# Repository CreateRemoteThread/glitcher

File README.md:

# glitcher

## Introduction

Glitcher is a homebrew fault injection system, built around a Pi Pico and CMOD A7, with a MAX4619 and an irf7807 providing multiplexer and crowbar mosfet style glitching respectively. Generous GPIO (FPGA + Pi Pico) + SMA outputs are available.

This project is heavily inspired by the ChipWhisperer set of products.

## Use

The Pi Pico is the simplest method of using this. Using a micro USB cable, access the MicroPython interface and use the glitcher library to control the FPGA's default firmware:

```
import glitcher

g = glitcher.Glitcher()
g.enablemux(True)                # enable max4619. crowbar always "on"
g.setmask(glitcher.SELECT_MOSFET)         # select mosfet for glitching
g.muxout(glitcher.SELECT_MUXA)            # switch x_out to x1
g.muxout(glitcher.SELECT_NONE)            # switch x_out to x0
g.rnr(delay=5,width=5)           # write delay/width, glitch output according to setmask
```

The Pi Pico uses only a serial port to talk to the FPGA at 115200bps, so you can swap it for some other uC / make a shield / whatever. Just replace self.u1 with a pyserial output if you want to use a control PC (enablemux is the only thing requiring the pi pico, just hardwire it idk).

Probably don't use g.muxout(0xF) - but do whatever you want.

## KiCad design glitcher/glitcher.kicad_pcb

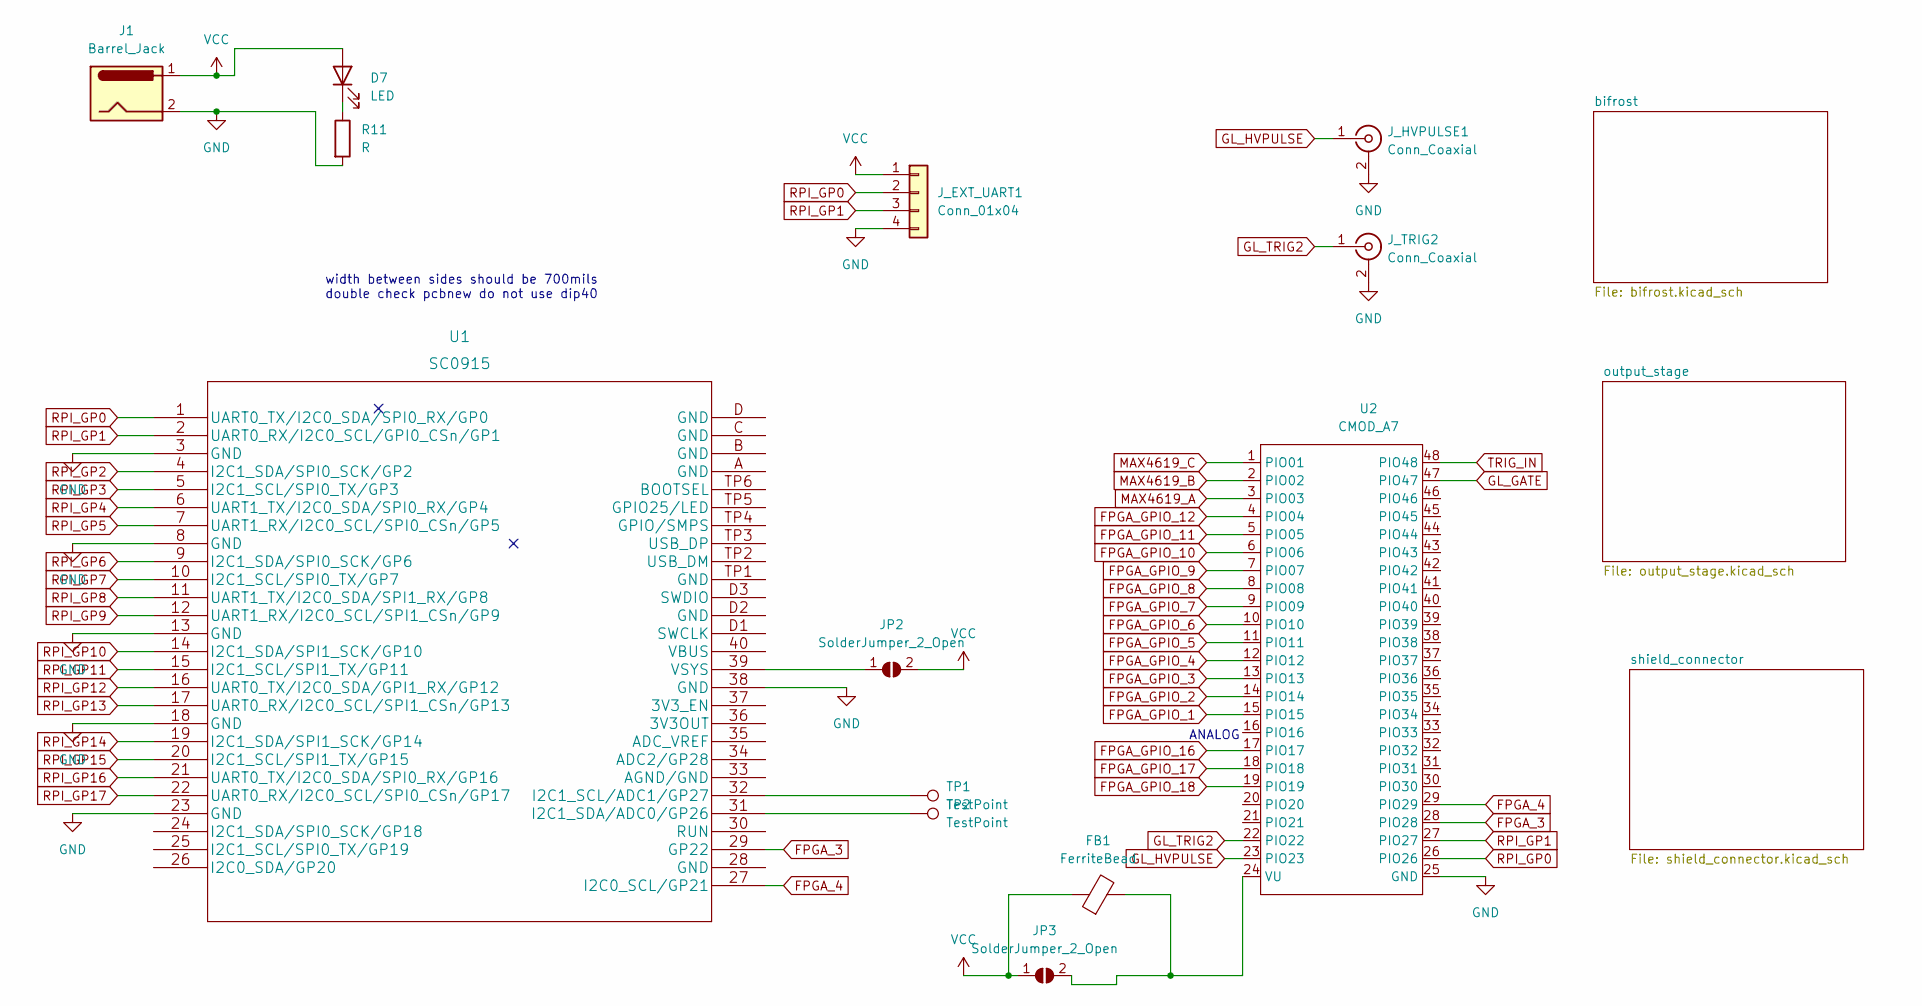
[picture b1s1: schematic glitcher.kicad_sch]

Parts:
D7: LED; LED_0603_1608Metric
FB1: FerriteBead; L_0805_2012Metric_Pad1.05x1.20mm_HandSolder
J1: Barrel_Jack; BarrelJack_Horizontal
JP2, JP3: SolderJumper_2_Open; SolderJumper-2_P1.3mm_Open_Pad1.0x1.5mm
J_EXT_UART1: Conn_01x04; PinHeader_1x04_P2.54mm_Vertical
J_HVPULSE1: Conn_Coaxial; RF2-04A-T-00-50-G
J_TRIG2: Conn_Coaxial; RF2-04A-T-00-50-G
R11: R; R_0603_1608Metric
TP1, TP2: TestPoint; TestPoint_Pad_D3.0mm
U1: SC0915; rpi_socket_fixed
U2: CMOD_A7; DIP-48_W15.24mm_Socket_LongPads

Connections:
FPGA_3: U1.29 (GP22), U2.28 (PIO28)
FPGA_4: U1.27 (I2C0_SCL/GP21), U2.29 (PIO29)
FPGA_GPIO_1: U2.15 (PIO15)
FPGA_GPIO_2: U2.14 (PIO14); also elsewhere on the board
FPGA_GPIO_3: U2.13 (PIO13); also elsewhere on the board
FPGA_GPIO_4: U2.12 (PIO12); also elsewhere on the board
FPGA_GPIO_5: U2.11 (PIO11); also elsewhere on the board
FPGA_GPIO_6: U2.10 (PIO10); also elsewhere on the board
FPGA_GPIO_7: U2.9 (PIO09); also elsewhere on the board
FPGA_GPIO_8: U2.8 (PIO08); also elsewhere on the board
FPGA_GPIO_9: U2.7 (PIO07); also elsewhere on the board
FPGA_GPIO_10: U2.6 (PIO06); also elsewhere on the board
FPGA_GPIO_11: U2.5 (PIO05); also elsewhere on the board
FPGA_GPIO_12: U2.4 (PIO04); also elsewhere on the board
FPGA_GPIO_16: U2.17 (PIO17); also elsewhere on the board
FPGA_GPIO_17: U2.18 (PIO18); also elsewhere on the board
FPGA_GPIO_18: U2.19 (PIO19); also elsewhere on the board
GL_GATE: U2.47 (PIO47); also elsewhere on the board
GL_HVPULSE: J_HVPULSE1.1 (In), U2.23 (PIO23)
GL_TRIG2: J_TRIG2.1 (In), U2.22 (PIO22)
GND: J1.2, J_EXT_UART1.4, J_HVPULSE1.2 (Ext), J_HVPULSE1.3, J_HVPULSE1.4, J_HVPULSE1.5, J_TRIG2.2 (Ext), J_TRIG2.3, J_TRIG2.4, J_TRIG2.5, R11.2, U1.3 (GND), U1.8 (GND), U1.13 (GND), U1.18 (GND), U1.23 (GND), U1.38 (GND), U2.25 (GND); also elsewhere on the board
MAX4619_A: U2.3 (PIO03); also elsewhere on the board
MAX4619_B: U2.2 (PIO02); also elsewhere on the board
MAX4619_C: U2.1 (PIO01); also elsewhere on the board
unnamed: D7.1 (K), R11.1
unnamed: FB1.2, JP3.2 (B), U2.24 (VU)
unnamed: JP2.1 (A), U1.39 (VSYS)
unnamed: TP1.1, U1.32 (I2C1_SCL/ADC1/GP27)
unnamed: TP2.1, U1.31 (I2C1_SDA/ADC0/GP26)
RPI_GP0: J_EXT_UART1.2, U1.1 (UART0_TX/I2C0_SDA/SPI0_RX/GP0), U2.26 (PIO26)
RPI_GP1: J_EXT_UART1.3, U1.2 (UART0_RX/I2C0_SCL/GPI0_CSn/GP1), U2.27 (PIO27)
RPI_GP2: U1.4 (I2C1_SDA/SPI0_SCK/GP2); also elsewhere on the board
RPI_GP3: U1.5 (I2C1_SCL/SPI0_TX/GP3); also elsewhere on the board
RPI_GP4: U1.6 (UART1_TX/I2C0_SDA/SPI0_RX/GP4); also elsewhere on the board
RPI_GP5: U1.7 (UART1_RX/I2C0_SCL/SPI0_CSn/GP5); also elsewhere on the board
RPI_GP6: U1.9 (I2C1_SDA/SPI0_SCK/GP6); also elsewhere on the board
RPI_GP7: U1.10 (I2C1_SCL/SPI0_TX/GP7); also elsewhere on the board
RPI_GP8: U1.11 (UART1_TX/I2C0_SDA/SPI1_RX/GP8); also elsewhere on the board
RPI_GP9: U1.12 (UART1_RX/I2C0_SCL/SPI1_CSn/GP9); also elsewhere on the board
RPI_GP10: U1.14 (I2C1_SDA/SPI1_SCK/GP10); also elsewhere on the board
RPI_GP11: U1.15 (I2C1_SCL/SPI1_TX/GP11); also elsewhere on the board
RPI_GP12: U1.16 (UART0_TX/I2C0_SDA/GPI1_RX/GP12); also elsewhere on the board
RPI_GP13: U1.17 (UART0_RX/I2C0_SCL/SPI1_CSn/GP13); also elsewhere on the board
RPI_GP14: U1.19 (I2C1_SDA/SPI1_SCK/GP14); also elsewhere on the board
RPI_GP15: U1.20 (I2C1_SCL/SPI1_TX/GP15); also elsewhere on the board
RPI_GP16: U1.21 (UART0_TX/I2C0_SDA/SPI0_RX/GP16)
RPI_GP17: U1.22 (UART0_RX/I2C0_SCL/SPI0_CSn/GP17)
TRIG_IN: U2.48 (PIO48); also elsewhere on the board
VCC: D7.2 (A), FB1.1, J1.1, JP2.2 (B), JP3.1 (A), J_EXT_UART1.1; also elsewhere on the board

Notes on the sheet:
width between sides should be 700mils double check pcbnew do not use dip40
ANALOG

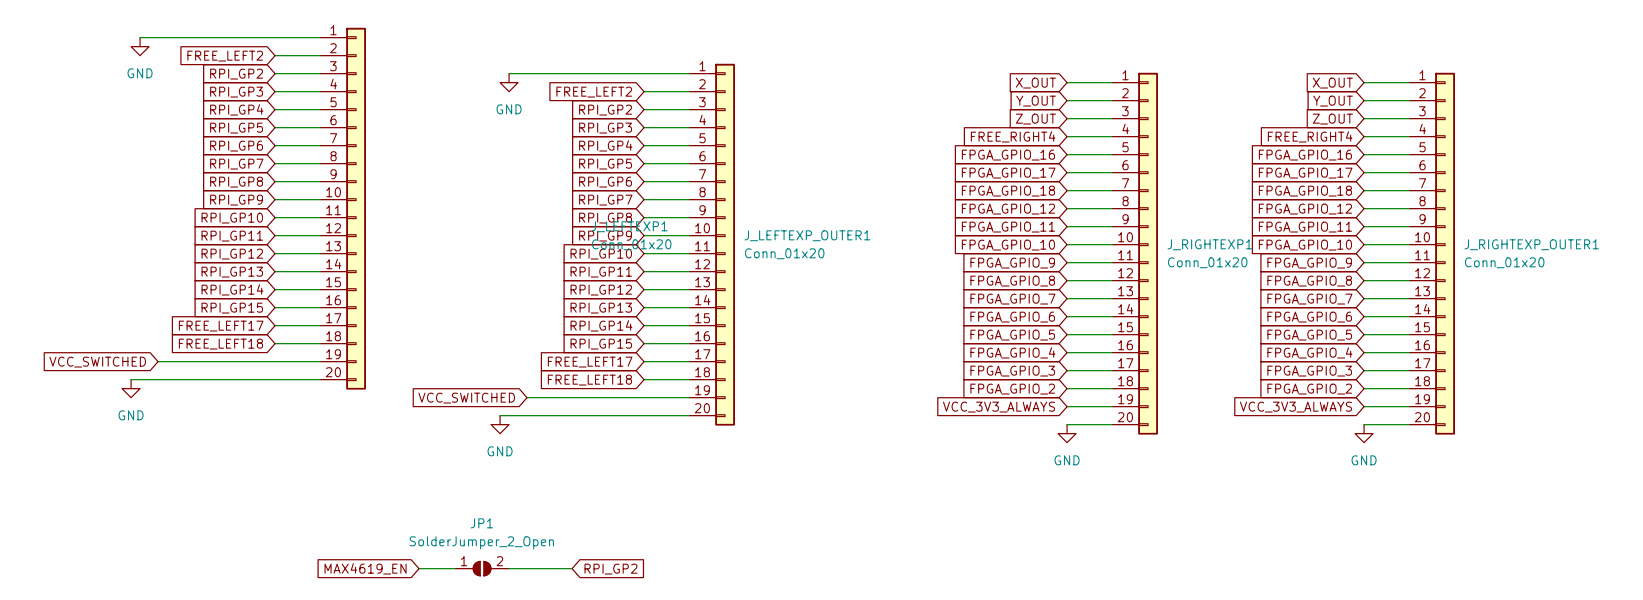
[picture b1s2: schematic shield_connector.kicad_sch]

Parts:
JP1: SolderJumper_2_Open; SolderJumper-2_P1.3mm_Open_RoundedPad1.0x1.5mm
J_LEFTEXP1: Conn_01x20; PinHeader_1x20_P2.54mm_Vertical
J_LEFTEXP_OUTER1: Conn_01x20; PinHeader_1x20_P2.54mm_Vertical
J_RIGHTEXP1: Conn_01x20; PinHeader_1x20_P2.54mm_Vertical
J_RIGHTEXP_OUTER1: Conn_01x20; PinHeader_1x20_P2.54mm_Vertical

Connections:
FPGA_GPIO_2: J_RIGHTEXP1.18, J_RIGHTEXP_OUTER1.18; also elsewhere on the board
FPGA_GPIO_3: J_RIGHTEXP1.17, J_RIGHTEXP_OUTER1.17; also elsewhere on the board
FPGA_GPIO_4: J_RIGHTEXP1.16, J_RIGHTEXP_OUTER1.16; also elsewhere on the board
FPGA_GPIO_5: J_RIGHTEXP1.15, J_RIGHTEXP_OUTER1.15; also elsewhere on the board
FPGA_GPIO_6: J_RIGHTEXP1.14, J_RIGHTEXP_OUTER1.14; also elsewhere on the board
FPGA_GPIO_7: J_RIGHTEXP1.13, J_RIGHTEXP_OUTER1.13; also elsewhere on the board
FPGA_GPIO_8: J_RIGHTEXP1.12, J_RIGHTEXP_OUTER1.12; also elsewhere on the board
FPGA_GPIO_9: J_RIGHTEXP1.11, J_RIGHTEXP_OUTER1.11; also elsewhere on the board
FPGA_GPIO_10: J_RIGHTEXP1.10, J_RIGHTEXP_OUTER1.10; also elsewhere on the board
FPGA_GPIO_11: J_RIGHTEXP1.9, J_RIGHTEXP_OUTER1.9; also elsewhere on the board
FPGA_GPIO_12: J_RIGHTEXP1.8, J_RIGHTEXP_OUTER1.8; also elsewhere on the board
FPGA_GPIO_16: J_RIGHTEXP1.5, J_RIGHTEXP_OUTER1.5; also elsewhere on the board
FPGA_GPIO_17: J_RIGHTEXP1.6, J_RIGHTEXP_OUTER1.6; also elsewhere on the board
FPGA_GPIO_18: J_RIGHTEXP1.7, J_RIGHTEXP_OUTER1.7; also elsewhere on the board
FREE_LEFT2: J_LEFTEXP1.2, J_LEFTEXP_OUTER1.2
FREE_LEFT17: J_LEFTEXP1.17, J_LEFTEXP_OUTER1.17
FREE_LEFT18: J_LEFTEXP1.18, J_LEFTEXP_OUTER1.18
FREE_RIGHT4: J_RIGHTEXP1.4, J_RIGHTEXP_OUTER1.4
GND: J_LEFTEXP1.1, J_LEFTEXP1.20, J_LEFTEXP_OUTER1.1, J_LEFTEXP_OUTER1.20, J_RIGHTEXP1.20, J_RIGHTEXP_OUTER1.20; also elsewhere on the board
MAX4619_EN: JP1.1 (A); also elsewhere on the board
RPI_GP2: JP1.2 (B), J_LEFTEXP1.3, J_LEFTEXP_OUTER1.3; also elsewhere on the board
RPI_GP3: J_LEFTEXP1.4, J_LEFTEXP_OUTER1.4; also elsewhere on the board
RPI_GP4: J_LEFTEXP1.5, J_LEFTEXP_OUTER1.5; also elsewhere on the board
RPI_GP5: J_LEFTEXP1.6, J_LEFTEXP_OUTER1.6; also elsewhere on the board
RPI_GP6: J_LEFTEXP1.7, J_LEFTEXP_OUTER1.7; also elsewhere on the board
RPI_GP7: J_LEFTEXP1.8, J_LEFTEXP_OUTER1.8; also elsewhere on the board
RPI_GP8: J_LEFTEXP1.9, J_LEFTEXP_OUTER1.9; also elsewhere on the board
RPI_GP9: J_LEFTEXP1.10, J_LEFTEXP_OUTER1.10; also elsewhere on the board
RPI_GP10: J_LEFTEXP1.11, J_LEFTEXP_OUTER1.11; also elsewhere on the board
RPI_GP11: J_LEFTEXP1.12, J_LEFTEXP_OUTER1.12; also elsewhere on the board
RPI_GP12: J_LEFTEXP1.13, J_LEFTEXP_OUTER1.13; also elsewhere on the board
RPI_GP13: J_LEFTEXP1.14, J_LEFTEXP_OUTER1.14; also elsewhere on the board
RPI_GP14: J_LEFTEXP1.15, J_LEFTEXP_OUTER1.15; also elsewhere on the board
RPI_GP15: J_LEFTEXP1.16, J_LEFTEXP_OUTER1.16; also elsewhere on the board
VCC_3V3_ALWAYS: J_RIGHTEXP1.19, J_RIGHTEXP_OUTER1.19; also elsewhere on the board
VCC_SWITCHED: J_LEFTEXP1.19, J_LEFTEXP_OUTER1.19; also elsewhere on the board
X_OUT: J_RIGHTEXP1.1, J_RIGHTEXP_OUTER1.1; also elsewhere on the board
Y_OUT: J_RIGHTEXP1.2, J_RIGHTEXP_OUTER1.2; also elsewhere on the board
Z_OUT: J_RIGHTEXP1.3, J_RIGHTEXP_OUTER1.3; also elsewhere on the board

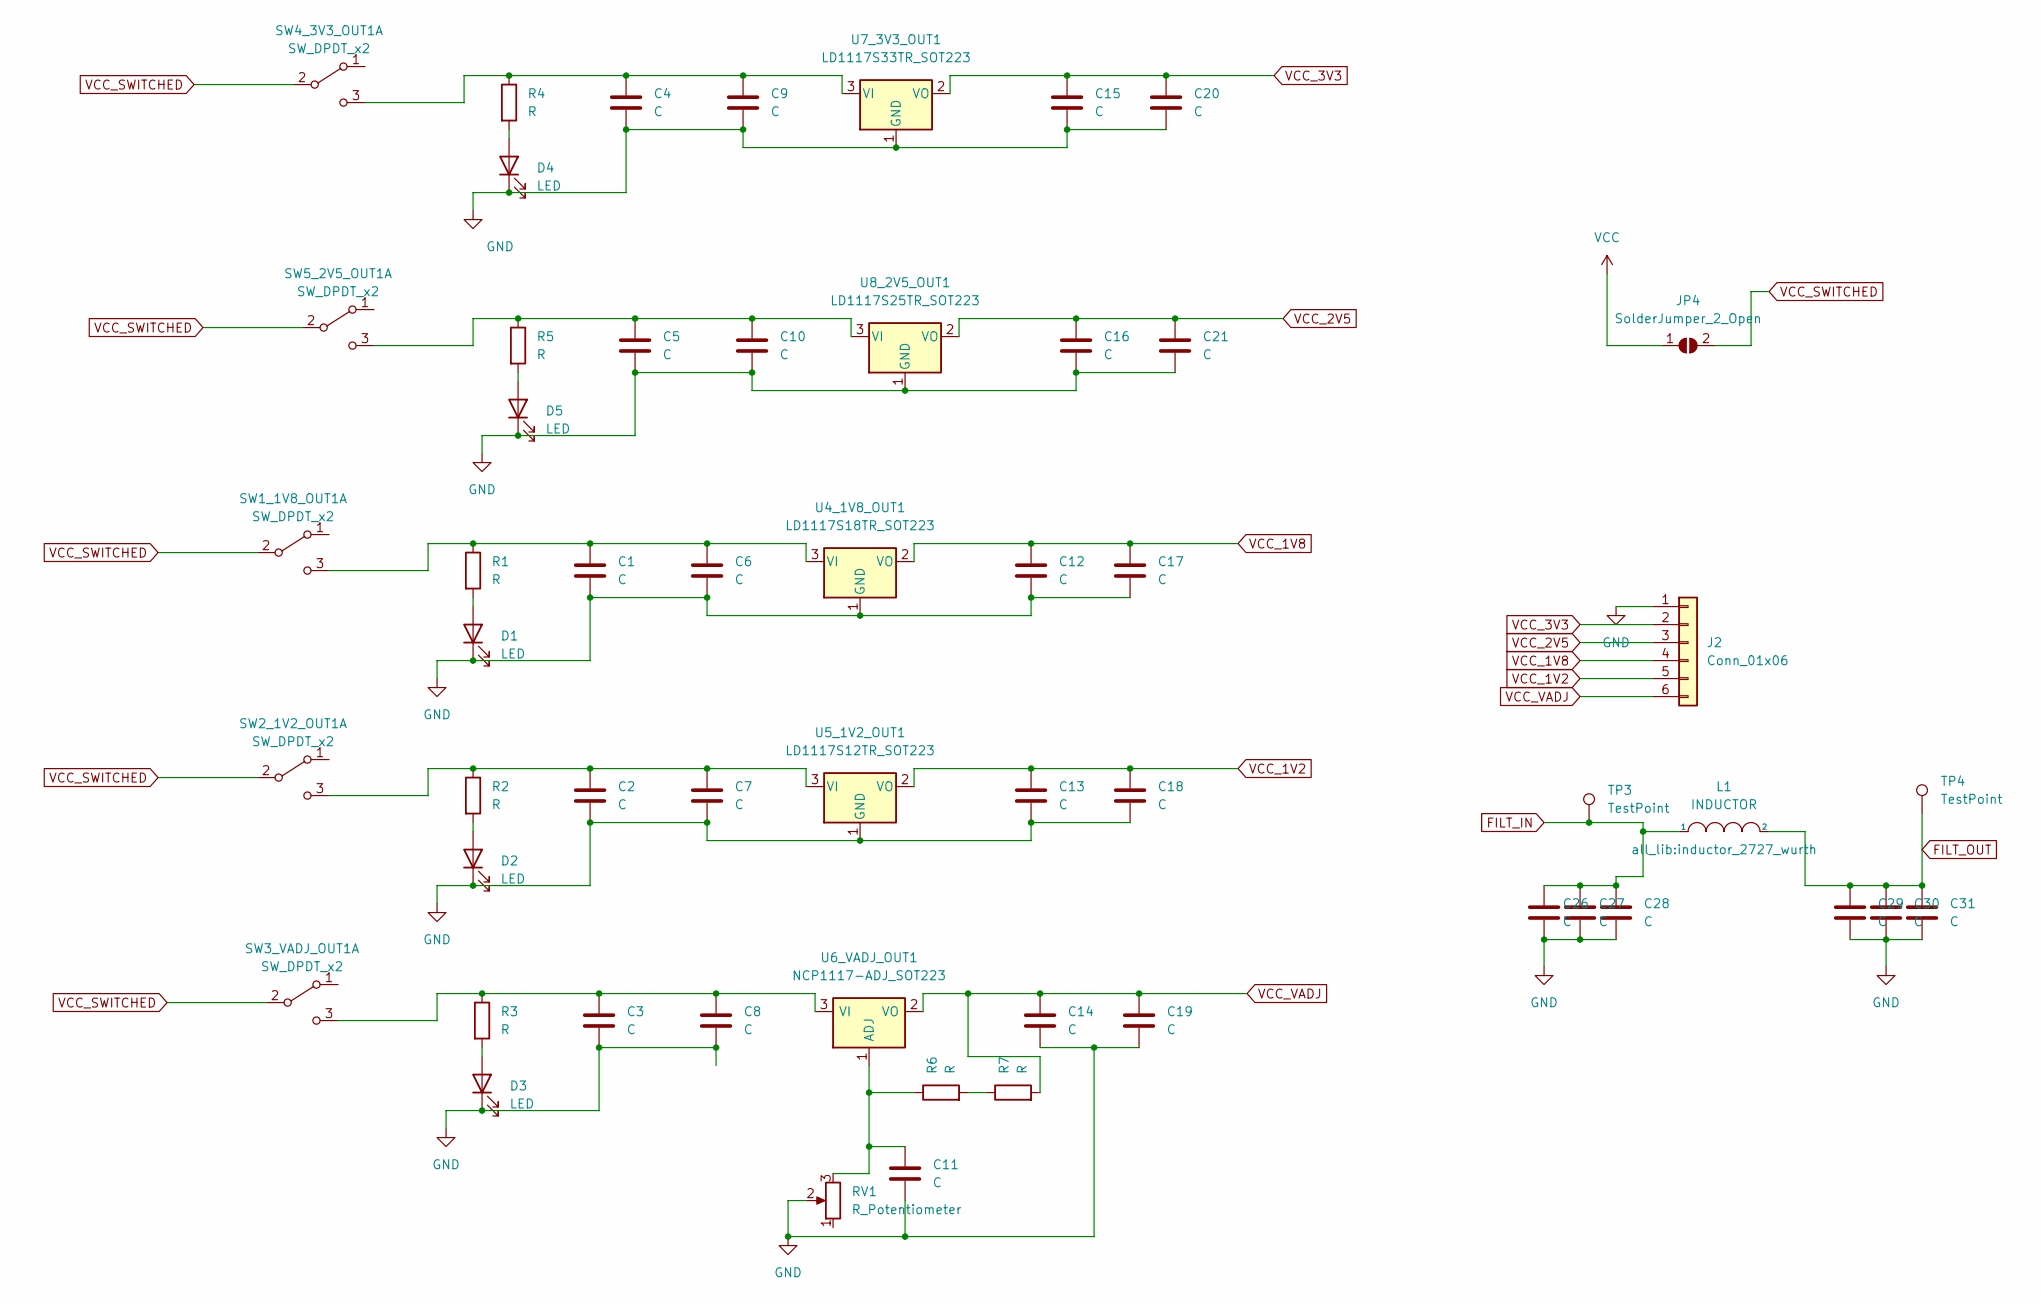
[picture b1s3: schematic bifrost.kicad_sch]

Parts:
C1, C2, C3, C4, C5, C6, C7, C8, C9, C10, C11, C12, C13, C14, C15, C16, C17, C18, C19, C20, C21, C26, C27, C28, C29, C30, C31: C; C_0603_1608Metric_Pad1.08x0.95mm_HandSolder
D1, D2, D3, D4, D5: LED; LED_0603_1608Metric_Pad1.05x0.95mm_HandSolder
J2: Conn_01x06; PinHeader_1x06_P2.54mm_Vertical
JP4: SolderJumper_2_Open; SolderJumper-2_P1.3mm_Open_RoundedPad1.0x1.5mm
L1: INDUCTOR; inductor_2727_wurth
R1, R2, R3, R4, R5, R6, R7: R; R_0603_1608Metric_Pad0.98x0.95mm_HandSolder
RV1: R_Potentiometer; TRIM_3361P-1-501GLF
SW1_1V8_OUT1, SW2_1V2_OUT1, SW3_VADJ_OUT1, SW4_3V3_OUT1, SW5_2V5_OUT1: SW_DPDT_x2; JS202011SCQN
TP3, TP4: TestPoint; TestPoint_Pad_D2.5mm
U4_1V8_OUT1: LD1117S18TR_SOT223; SOT-223-3_TabPin2
U5_1V2_OUT1: LD1117S12TR_SOT223; SOT-223-3_TabPin2
U6_VADJ_OUT1: NCP1117-ADJ_SOT223; SOT-223-3_TabPin2
U7_3V3_OUT1: LD1117S33TR_SOT223; SOT-223-3_TabPin2
U8_2V5_OUT1: LD1117S25TR_SOT223; SOT-223-3_TabPin2

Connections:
FILT_IN: C26.1, C27.1, C28.1, L1.1, TP3.1
FILT_OUT: C29.1, C30.1, C31.1, L1.2, TP4.1
GND: C1.2, C2.2, C3.2, C4.2, C5.2, C6.2, C7.2, C8.2, C9.2, C10.2, C11.2, C12.2, C13.2, C14.2, C15.2, C16.2, C17.2, C18.2, C19.2, C20.2, C21.2, C26.2, C27.2, C28.2, C29.2, C30.2, C31.2, D1.1 (K), D2.1 (K), D3.1 (K), D4.1 (K), D5.1 (K), J2.1, RV1.2, U4_1V8_OUT1.1 (GND), U5_1V2_OUT1.1 (GND), U7_3V3_OUT1.1 (GND), U8_2V5_OUT1.1 (GND); also elsewhere on the board
unnamed: C1.1, C6.1, R1.1, SW1_1V8_OUT1.3 (C), U4_1V8_OUT1.3 (VI)
unnamed: C2.1, C7.1, R2.1, SW2_1V2_OUT1.3 (C), U5_1V2_OUT1.3 (VI)
unnamed: C3.1, C8.1, R3.1, SW3_VADJ_OUT1.3 (C), U6_VADJ_OUT1.3 (VI)
unnamed: C4.1, C9.1, R4.1, SW4_3V3_OUT1.3 (C), U7_3V3_OUT1.3 (VI)
unnamed: C5.1, C10.1, R5.1, SW5_2V5_OUT1.3 (C), U8_2V5_OUT1.3 (VI)
unnamed: C11.1, R6.1, RV1.3, U6_VADJ_OUT1.1 (ADJ)
unnamed: D1.2 (A), R1.2
unnamed: D2.2 (A), R2.2
unnamed: D3.2 (A), R3.2
unnamed: D4.2 (A), R4.2
unnamed: D5.2 (A), R5.2
unnamed: R6.2, R7.1
VCC: JP4.1 (A); also elsewhere on the board
VCC_1V2: C13.1, C18.1, J2.5, U5_1V2_OUT1.2 (VO)
VCC_1V8: C12.1, C17.1, J2.4, U4_1V8_OUT1.2 (VO)
VCC_2V5: C16.1, C21.1, J2.3, U8_2V5_OUT1.2 (VO)
VCC_3V3: C15.1, C20.1, J2.2, U7_3V3_OUT1.2 (VO)
VCC_SWITCHED: JP4.2 (B), SW1_1V8_OUT1.2 (B), SW2_1V2_OUT1.2 (B), SW3_VADJ_OUT1.2 (B), SW4_3V3_OUT1.2 (B), SW5_2V5_OUT1.2 (B); also elsewhere on the board
VCC_VADJ: C14.1, C19.1, J2.6, R7.2, U6_VADJ_OUT1.2 (VO)

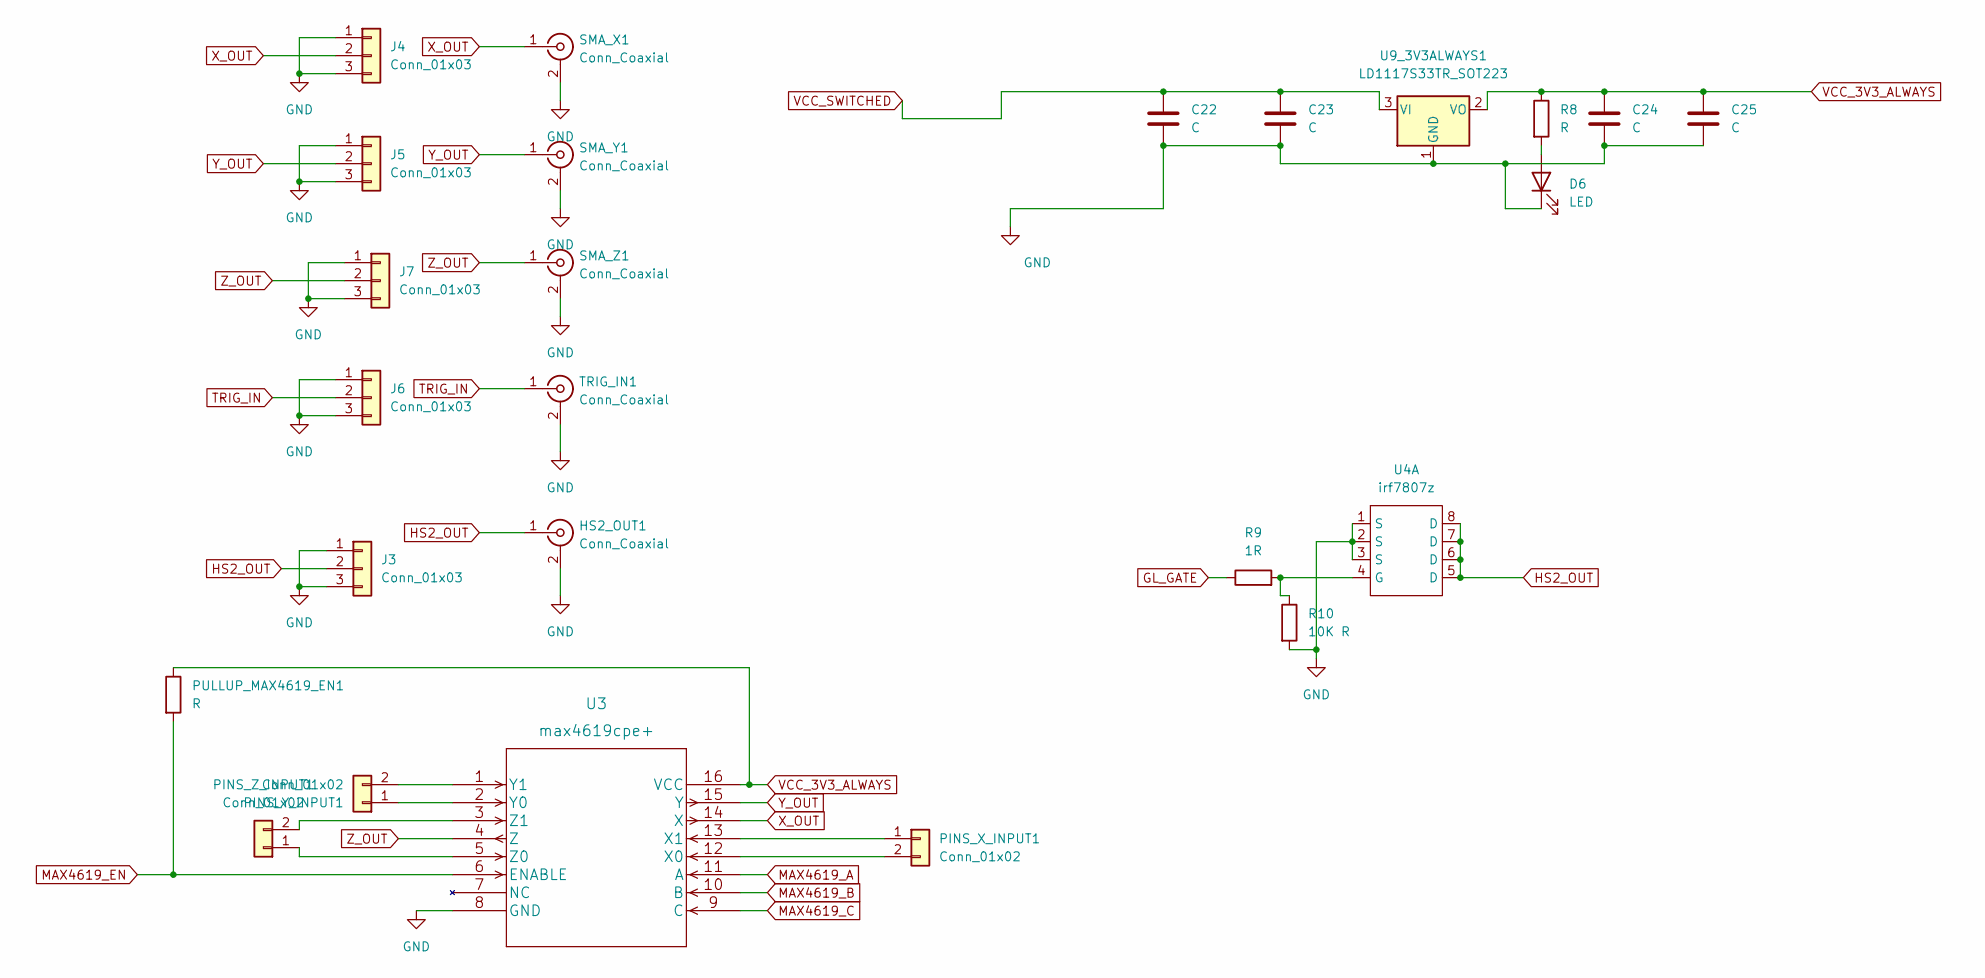
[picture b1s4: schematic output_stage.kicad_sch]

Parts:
C22, C23, C24, C25: C; C_0603_1608Metric_Pad1.08x0.95mm_HandSolder
D6: LED; LED_0603_1608Metric_Pad1.05x0.95mm_HandSolder
HS2_OUT1: Conn_Coaxial; SMA_Molex_73251-2120_EdgeMount_Horizontal
J3, J4, J5, J6, J7: Conn_01x03; PinHeader_1x03_P2.54mm_Vertical
PINS_X_INPUT1: Conn_01x02; PinHeader_1x02_P2.54mm_Vertical
PINS_Y_INPUT1: Conn_01x02; PinHeader_1x02_P2.54mm_Vertical
PINS_Z_INPUT1: Conn_01x02; PinHeader_1x02_P2.54mm_Vertical
PULLUP_MAX4619_EN1: R; R_0603_1608Metric_Pad0.98x0.95mm_HandSolder
R8: R; R_0603_1608Metric_Pad0.98x0.95mm_HandSolder
R9: 1R; R_0603_1608Metric_Pad0.98x0.95mm_HandSolder
R10: 10K R; R_0603_1608Metric_Pad0.98x0.95mm_HandSolder
SMA_X1: Conn_Coaxial; SMA_Molex_73251-2120_EdgeMount_Horizontal
SMA_Y1: Conn_Coaxial; SMA_Molex_73251-2120_EdgeMount_Horizontal
SMA_Z1: Conn_Coaxial; SMA_Molex_73251-2120_EdgeMount_Horizontal
TRIG_IN1: Conn_Coaxial; SMA_Molex_73251-2120_EdgeMount_Horizontal
U3: max4619cpe+; DIP-16_W7.62mm_Socket_LongPads
U4: irf7807z; SOIC-8-1EP_3.9x4.9mm_P1.27mm_EP2.29x3mm
U9_3V3ALWAYS1: LD1117S33TR_SOT223; SOT-223-3_TabPin2

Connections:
GL_GATE: R9.1; also elsewhere on the board
GND: C22.2, C23.2, C24.2, C25.2, D6.1 (K), HS2_OUT1.2 (Ext), J3.1, J3.3, J4.1, J4.3, J5.1, J5.3, J6.1, J6.3, J7.1, J7.3, R10.2, SMA_X1.2 (Ext), SMA_Y1.2 (Ext), SMA_Z1.2 (Ext), TRIG_IN1.2 (Ext), U3.8 (GND), U4.1 (S), U4.2 (S), U4.3 (S), U9_3V3ALWAYS1.1 (GND); also elsewhere on the board
HS2_OUT: HS2_OUT1.1 (In), J3.2, U4.5 (D), U4.6 (D), U4.7 (D), U4.8 (D)
MAX4619_A: U3.11 (A); also elsewhere on the board
MAX4619_B: U3.10 (B); also elsewhere on the board
MAX4619_C: U3.9 (C); also elsewhere on the board
MAX4619_EN: PULLUP_MAX4619_EN1.2, U3.6 (ENABLE); also elsewhere on the board
unnamed: D6.2 (A), R8.2
unnamed: PINS_X_INPUT1.1, U3.13 (X1)
unnamed: PINS_X_INPUT1.2, U3.12 (X0)
unnamed: PINS_Y_INPUT1.1, U3.2 (Y0)
unnamed: PINS_Y_INPUT1.2, U3.1 (Y1)
unnamed: PINS_Z_INPUT1.1, U3.5 (Z0)
unnamed: PINS_Z_INPUT1.2, U3.3 (Z1)
unnamed: R9.2, R10.1, U4.4 (G)
TRIG_IN: J6.2, TRIG_IN1.1 (In); also elsewhere on the board
VCC_3V3_ALWAYS: C24.1, C25.1, PULLUP_MAX4619_EN1.1, R8.1, U3.16 (VCC), U9_3V3ALWAYS1.2 (VO); also elsewhere on the board
VCC_SWITCHED: C22.1, C23.1, U9_3V3ALWAYS1.3 (VI); also elsewhere on the board
X_OUT: J4.2, SMA_X1.1 (In), U3.14 (X); also elsewhere on the board
Y_OUT: J5.2, SMA_Y1.1 (In), U3.15 (Y); also elsewhere on the board
Z_OUT: J7.2, SMA_Z1.1 (In), U3.4 (Z); also elsewhere on the board

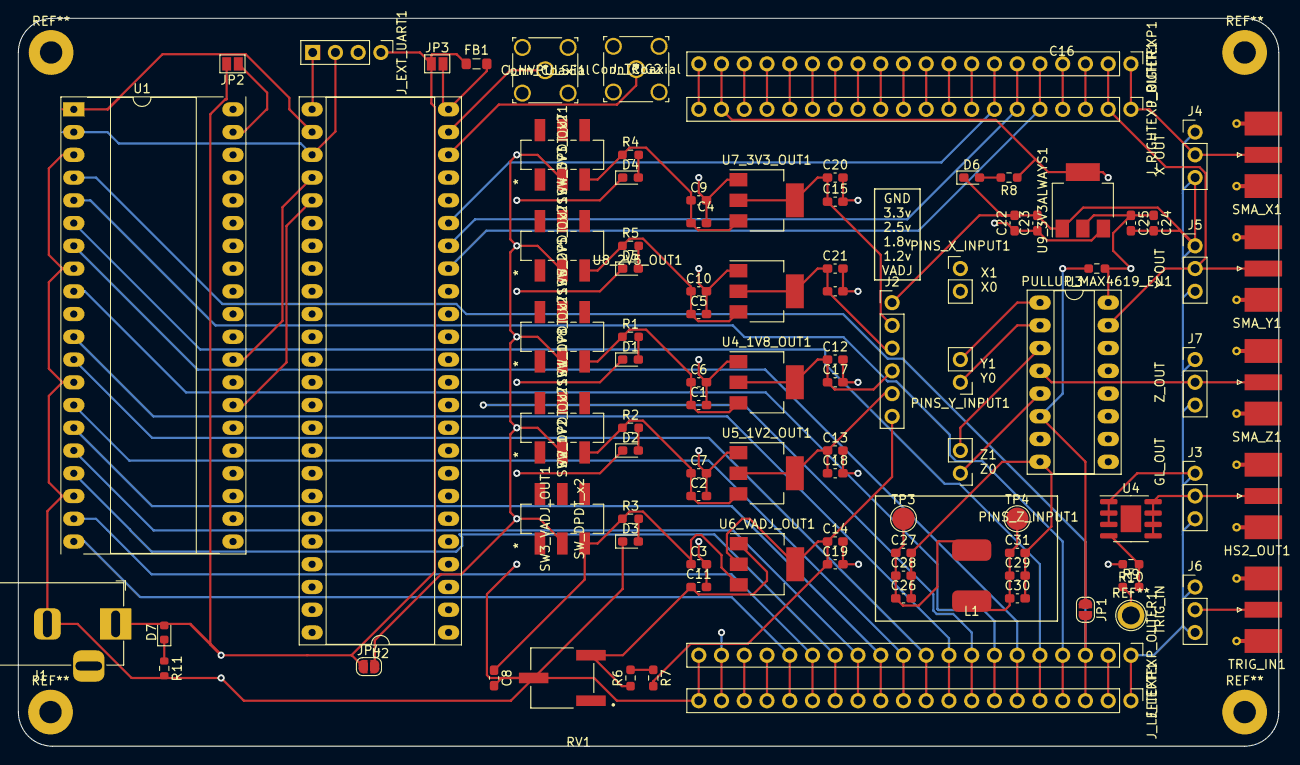
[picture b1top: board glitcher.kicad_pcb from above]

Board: 6 copper layers, 140.8 x 81.3 mm, 96 parts (0 on the bottom side), 82 nets.

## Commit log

2022-07-18 save
2022-07-19 lolsave
2022-07-21 prod1
2022-08-18 pewpew
2022-08-25 micropython
2022-08-25 upy update
2022-08-25 fpga update
2022-09-03 workbench shield thingy
2022-09-07 protoboard shield
2022-09-13 implemented g.muxout, python fixes
2022-09-13 save: baudrate
2022-12-31 updates for auxout, prep for clkout
2023-01-02 avr isp
2023-01-03 now with upl
2023-01-08 micropy
2023-01-08 micropy avr
2023-01-29 avr fixes
2023-01-30 pic test wip, do not actually use lol
2023-02-07 py workaround for mistake - muxc <-> muxb
2023-02-08 verilog update i guess
2023-02-08 verilog / py fixes for param edgetgt
2023-02-11 undo muxb/muxc change
2023-02-14 attiny fix
2023-02-27 quiet= option for automation
2023-04-16 xdc file
2025-01-03 fix: xbit on send mchp key
2025-01-08 fpga force-out-from-micropython update
2025-01-16 rp2040 -> l2 muxout tweak
2025-01-18 pio large register hack
2025-01-18 autofuzz fix
2025-01-18 edge cases handling
2025-01-18 I'm an idiot
2025-01-21 fuck
2025-01-28 shieldv3p1

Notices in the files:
parts and their libraries:
Copyright 2021 Accelerated Designs. All rights reserved.
